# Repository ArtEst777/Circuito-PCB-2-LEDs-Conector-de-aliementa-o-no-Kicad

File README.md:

PCB 2 LEDs desenvolvido no KiCAD
---------------

## Visualização 3D

## Esquemático

Descrição Geral
---------------
Este projeto consiste em uma placa de circuito impresso (PCB) simples que acende dois LEDs (um vermelho e um verde) a partir de uma fonte de alimentação de 5V. O circuito utiliza dois resistores de 100 ohms para limitar a corrente dos LEDs e um plano de terra na camada inferior (B.Cu) para simplificar o roteamento e melhorar a integridade do sinal.

O projeto foi desenvolvido no KiCad 10.0 como um exercício de aprendizado do fluxo completo de design de PCBs: criação do esquemático, associação de footprints, layout da placa, verificação de regras elétricas e de design, geração de arquivos Gerber e visualização 3D.

Esquemático
-----------
O esquemático (arquivo .kicad_sch) contém os seguintes componentes:

- J1: Conector de dois pinos (Conn_01x02_Male) para a entrada de alimentação 5V. O pino 1 é conectado à rede +5V e o pino 2 ao GND.
- R1, R2: Resistores de 100 ohms, 1/4W, com encapsulamento axial (THT). Cada resistor tem uma extremidade ligada ao +5V e a outra ao ânodo do LED correspondente.
- D1: LED vermelho difuso de 5mm. Ânodo conectado a R1, cátodo ligado ao GND.
- D2: LED verde difuso de 5mm. Ânodo conectado a R2, cátodo ligado ao GND.

Símbolos globais de alimentação (+5V e GND) são utilizados para distribuir a energia de forma organizada. O terra é comum a todos os componentes, formando uma única rede GND.

Cálculo da corrente nos LEDs:
Considerando uma tensão direta típica de 2,0V para o LED vermelho e 2,2V para o verde, a corrente em cada LED é:
  LED vermelho: (5V - 2,0V) / 100Ω = 30mA
  LED verde:   (5V - 2,2V) / 100Ω = 28mA
Ambos os valores estão dentro da faixa segura para LEDs de 5mm (geralmente 20-30mA), garantindo luminosidade adequada sem risco de danos.

A verificação de regras elétricas (ERC) retornou zero erros e zero avisos, indicando que todas as conexões estão corretas.

Lista de Materiais (BOM)
-------------------------
- 1x LED vermelho 5mm (D1)
- 1x LED verde 5mm (D2)
- 2x Resistor 100Ω, 1/4W, THT (R1, R2)
- 1x Barra de pinos macho 1x2, passo 2,54mm (J1) — ou borne de parafusos compatível
- 1x Placa de circuito impresso (obtida a partir dos arquivos Gerber fornecidos)
- Fonte de alimentação 5V (ex.: carregador USB, bateria com regulador)

Design da PCB
--------------
O layout da placa (arquivo .kicad_pcb) foi desenvolvido no Pcbnew. A placa tem formato retangular de aproximadamente 40mm x 30mm, definido na camada Edge.Cuts.

Características principais do layout:

1. Plano de terra (zona de cobre) na camada inferior (B.Cu):
   - Foi criada uma zona de cobre preenchida em B.Cu, associada à rede GND.
   - Essa zona conecta automaticamente todos os pads pertencentes ao GND (catodo dos LEDs e pino 2 do conector), eliminando a necessidade de trilhas de terra adicionais.
   - A zona foi configurada com alívios térmicos (espaçamento de 0,5mm) para facilitar a soldagem.
   - Isolamento mínimo de 0,5mm entre a zona e outros elementos.

2. Roteamento:
   - A única trilha desenhada manualmente foi a de +5V, na camada superior (F.Cu), ligando o pino 1 do conector aos resistores R1 e R2.
   - Largura de trilha: 0,5mm, suficiente para as correntes envolvidas.

3. Posicionamento dos componentes:
   - Conector J1 na borda esquerda da placa.
   - Resistores no centro, ligando o +5V aos ânodos dos LEDs.
   - LEDs na borda direita, com os catodos voltados para baixo (conectados internamente ao plano de terra).
   - Serigrafia (F.Silkscreen) indica a polaridade do conector e identifica cada LED.

4. Verificações de design (DRC):
   - Antes de executar o DRC, a zona de cobre foi preenchida (tecla B).
   - O DRC retornou 0 violações, confirmando que o layout atende às regras de fabricação.

Alguns testes foram ignorados pelo DRC (ex.: "footprint não bate com o filtro da biblioteca"), o que é comum e não afeta o funcionamento.

Visualização 3D
----------------
O visualizador 3D do KiCad foi utilizado para inspecionar a placa virtualmente. Observações:
- Por padrão, ambos os LEDs aparecem na cor vermelha, pois o modelo 3D genérico (LED_D5.0mm) não distingue cores. Isso é apenas cosmético; os LEDs reais terão as cores conforme adquiridos.
- Para alterar a cor no modelo 3D, seria necessário substituir o arquivo STEP de um dos LEDs por uma versão colorida (ex.: LED_D5.0mm_Green.step), se disponível na biblioteca.
- O plano de terra em B.Cu é visível ao girar a placa e habilitar a camada B.Cu nas opções de exibição do visualizador 3D.

Arquivos de Fabricação (Gerber e Excellon)
------------------------------------------
Os arquivos para fabricação da PCB estão na pasta "Arquivo_Gerber/" e incluem:

Camadas Gerber (formato RS-274X, X2 estendido):
- Circuito_2_Leds_dos_crias_mecatronicos-F_Cu.gbr         -> Cobre superior
- Circuito_2_Leds_dos_crias_mecatronicos-B_Cu.gbr         -> Cobre inferior (plano de terra)
- Circuito_2_Leds_dos_crias_mecatronicos-F_Mask.gbr       -> Máscara de solda superior
- Circuito_2_Leds_dos_crias_mecatronicos-B_Mask.gbr       -> Máscara de solda inferior
- Circuito_2_Leds_dos_crias_mecatronicos-F_Silkscreen.gbr -> Serigrafia superior
- Circuito_2_Leds_dos_crias_mecatronicos-B_Silkscreen.gbr -> Serigrafia inferior (opcional)
- Circuito_2_Leds_dos_crias_mecatronicos-Edge_Cuts.gbr    -> Contorno da placa

Arquivo de furação (Excellon):
- Circuito_2_Leds_dos_crias_mecatronicos.drl              -> Coordenadas dos furos, unidades em mm, formato decimal

Para encomendar a placa, compacte todos os arquivos da pasta "Arquivo_Gerber/" em um arquivo .zip e envie ao fabricante de sua preferência (JLCPCB, PCBWay, etc.).

Montagem e Teste
-----------------
1. Solde os resistores R1 e R2.
2. Solde os LEDs D1 (vermelho) e D2 (verde), respeitando a polaridade: o terminal mais longo (ânodo) deve ser conectado ao resistor; o terminal mais curto (cátodo) ao plano de terra.
3. Solde o conector J1.
4. Conecte uma fonte de 5V, observando a polaridade indicada na serigrafia.
5. Ambos os LEDs devem acender imediatamente.

Se um LED não acender, verifique:
- Se a solda está firme e sem curto-circuito.
- Se o LED não foi invertido (polaridade trocada).
- Se a fonte está fornecendo 5V estáveis.

Possíveis Melhorias Futuras
----------------------------
- Adicionar um botão liga/desliga em série com a alimentação.
- Substituir o conector de pinos por um conector USB (ex.: micro-USB ou USB-C).
- Incluir um resistor de pull-down ou proteção contra inversão de polaridade.
- Criar uma versão com controle independente de cada LED via microcontrolador (ex.: ESP32, Arduino).

Estrutura do Repositório (Sugestão)
-------------------------------------
Circuito_2_Leds_dos_crias_mecatronicos/
├── README.txt (este arquivo)
├── Circuito_2_Leds_dos_crias_mecatronicos.kicad_pro
├── Circuito_2_Leds_dos_crias_mecatronicos.kicad_sch
├── Circuito_2_Leds_dos_crias_mecatronicos.kicad_pcb
├── .gitignore
├── Arquivo_Gerber/
│   ├── Circuito_2_Leds_dos_crias_mecatronicos-F_Cu.gbr
│   ├── Circuito_2_Leds_dos_crias_mecatronicos-B_Cu.gbr
│   ├── Circuito_2_Leds_dos_crias_mecatronicos-F_Mask.gbr
│   ├── Circuito_2_Leds_dos_crias_mecatronicos-B_Mask.gbr
│   ├── Circuito_2_Leds_dos_crias_mecatronicos-F_Silkscreen.gbr
│   ├── Circuito_2_Leds_dos_crias_mecatronicos-B_Silkscreen.gbr
│   ├── Circuito_2_Leds_dos_crias_mecatronicos-Edge_Cuts.gbr
│   └── Circuito_2_Leds_dos_crias_mecatronicos.drl
└── doc/ (opcional)
    ├── esquematico.pdf
    ├── pcb_frente.pdf
    ├── pcb_costas.pdf
    └── pcb_3d.png

Contato e Suporte
-------------------
Este projeto faz parte do aprendizado em engenharia mecatrônica e robótica. Se você tiver dúvidas, sugestões ou quiser trocar ideias sobre design de PCBs, fique à vontade para abrir uma issue no repositório do GitHub (link do repositório) ou entrar em contato diretamente.

Se você está usando este repositório como base para seus próprios estudos, recomendo os seguintes recursos:
- Documentação oficial do KiCad: https://docs.kicad.org
- Fórum da comunidade KiCad: https://forum.kicad.info
- Canais no YouTube sobre KiCad e eletrônica.

O desenvolvimento desse projeto teve auxílio de um chat de IA, deepseek, que me auxiliou na elaboração desta documentação e na solução de dúvidas durante o desenvolvimento do projeto.

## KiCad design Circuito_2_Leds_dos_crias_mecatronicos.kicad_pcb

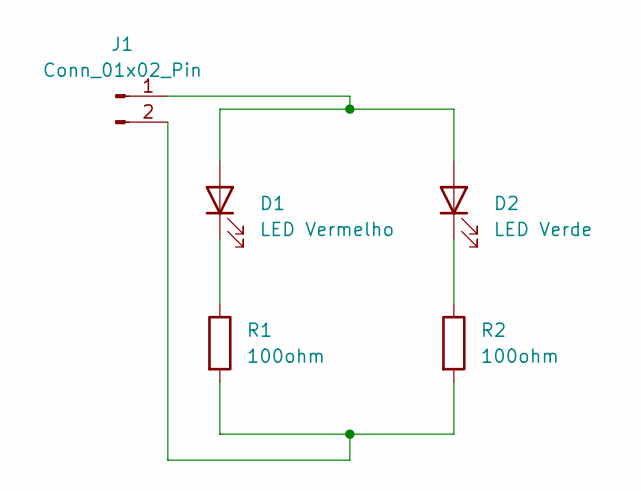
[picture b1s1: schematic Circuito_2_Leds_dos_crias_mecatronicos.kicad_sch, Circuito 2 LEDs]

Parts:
D1: LED Vermelho; LED_D5.0mm
D2: LED Verde; LED_D5.0mm
J1: Conn_01x02_Pin; PinHeader_1x02_P2.54mm_Vertical
R1, R2: 100ohm; R_Axial_DIN0207_L6.3mm_D2.5mm_P2.54mm_Vertical

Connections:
unnamed: D1.2 (A), D2.2 (A), J1.1
unnamed: D1.1 (K), R1.1
unnamed: D2.1 (K), R2.1
unnamed: J1.2, R1.2, R2.2

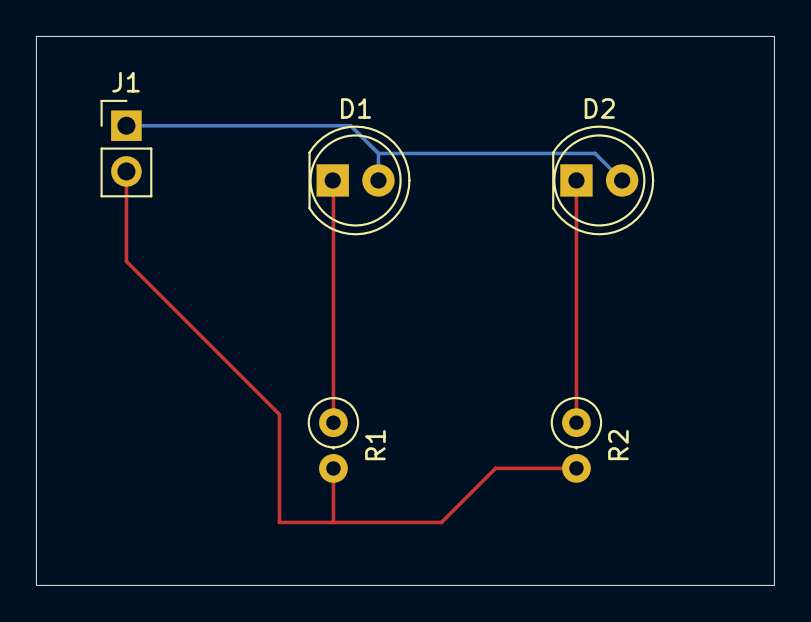
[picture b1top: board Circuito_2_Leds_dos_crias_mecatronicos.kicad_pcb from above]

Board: 2 copper layers, 41.0 x 30.5 mm, 5 parts (0 on the bottom side), 4 nets.
